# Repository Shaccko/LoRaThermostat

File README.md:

# LoRaThermostat
A 24V HVAC designed Thermostat built using the STM32 F103C8T6

By Ghanim

This is my first big capstone project, and it was done over the course of my final 
year in computer science. Unfortunately no git commits since I wasn't wise enough
back then to have initialized this project with git, so it's as raw as it gets.

This was made out of necessity, not as a desire to learn (which changed over its duration)
because my thermostat at home was 8 steps away from my room, and I hated having to get up
and change it manually due to people at my home constantly changing it. I thought it would
be nice to have a thermostat with a remote, and coincidentally at the time I was just getting
into my very first introduction to embedded design thats not arduino, with the STM32. I was also
incredibly curious as to how people exactly make the transition from MCU prototype to actual
PCB design.

# Device/Components used
# STM32 F103C8T6
For the MCU, initially I went way overkill and started with the F746ZGT6U family,
which provided 1MB flash and 512kb sram, incredibly overkill with what 
the project intended to be. As I moved to PCB design, this was switched to the F103
family for reduced chip cost, and redo'ing pretty much everything.

# LoRa
This was also my first introduction to LoRa, it was perfect for what my design was
intended for, a transmitter (remote) transmitting at most up to 10 bytes intended
for long range uses. I used a random LoRa library online I found at the time, since
bits were too scary to work with, although going back I definitely wish I'd have
read the LoRa datasheet atleast since it would have shown me different optimization modes
LoRa offers, like sleep mode, receiving a single packet, optimizing current draw etc.

# Si7021/JHD204a
To actually read and display temperature, I used the Si7021 Honeywell module, and the JHD204a
20x4 liquid crystal, controlling both with their own library I found online. 

# Main application design
I wish I did initialize this project with git when I started, because it really would be nice to look
at how disorganized my code first seemed compared to how it is now (relatively, atleast).
Receiver and Transmitter are separated under their own projects. 
Transmitter and receiver both run a state machine and constantly check for LoRa commands from either side.
Transmitter sends a metadata guarded buffer via LoRa to be decoded by receiver. The thermostat goes to sleep
if no commands are received within a duration, the MCU goes to sleep 
by employing STM32's STOP mode, turns off LCD backlight, and wakes up via external interrupts/every 50 seconds. 
STOP mode was configured so as to save as much power as possible during moments of no operations, even though LoRa being in receive continuous mode 
draws moderately more power, the MCU balances its own current draw by going to sleep. 

Temperature is moderated using a 'deadzone' mechanic so as to prevent rapid cool/heat furnace mode which could cause issues. If temperature
is set to cool or heat, but below/above its setpoint, it waits till it crosses setpoint plus or minus its deadzone, then
only it turns on either heat or ac. For the small duration it wakes up, it sends current temperature data back to transmitter,
making sure both modules are in sync. This design philosophy was inspired by observing my current Honeywell thermostat.

# PCB/Schematic Design
This portion took pretty much 60% of the total project time. It was my first introduction to 
pcb design and I wanted to be absolutely 100% sure that I wouldn't mess anything up (due to 
high pcb design cost, atleast from JLCPCB) , and took my time learning the basics of 
electronic design.

# STM32 Schematic
Following Phils Lab intro to KiCad with STM32 guide, I was able to make initial
schematic designs that fit the bare essentials of what a PCB with an embedded MCU would need: crystal,
capacitors, boot modes, and power supply. 

# Transmitter (Remote)
# Transmitter MCU

A 100n capacitor is installed per VDD pin, as per STM32's MCU design guide. An 8MHz crystal is used, matching what my MCU
prototype was using, and a boot mode switch, which pulls BOOT0 either high or low depending on programming/flash mode.
To program it, we use ST-LINK, 4 male pins are exposed to STM32's SWCLK and SWDIO for programming.
Receiver's MCU looks exact same, only difference is different pinout locations. 

# Power Supply

Simple USB-C 5.0V to 3.3V power supply. Uses a cheap LDO regulator, the AMS1117-3.3v to convert 5.0v to 3.3v.

# Components

Other than buttons, both LoRa and the JHD204a LCD were substituted with female header pins for budget reasons; I already
had their respective breakout modules at home, so it was a matter of just simply attaching them to their respective headers.

# Receiver (Thermostat)
# Receiver MCU
Same as transmitter.

# Power supply

Our thermostat wants to be attached to a wall practically, so I went with a 2x Double A battery as input. This in turn is supplied to a 
boost convertor, texas instruments TPS6104 that ramps up voltage to 5.0v, and back to a stable 3.3v using the same LDO regulator to supply 
a stable 3.3v to our circuit. Looking back at it, a separate power supply strategy using batteries should have been used instead,
converting to 5.0v then back to 3.3v is definitely not ideal. Regardless, when I was designing this, I made sure to ensure that I would
achieve atleast 90% efficiency. TPS6104 is designed to be quiescient, meaning minimal battery current usage during stages of low circuit
overall draw. 

# Triac -> SSR for HVAC Routing

This circuit is responsible for safely sending MCU high/low signals to our HVAC24 system. If heat/cool signals high, voltage reaches
our opto-triac, which in turn signals our triac to open gate and let flow 24V from R line from our furnace. Every half-cycle it checks
if signal is high, and as soon as MCU signals low, on its next half-cycle, the triac will shut its gate down and not let current flow.

Previously, I had a much simpler relay design in mind, where I would use a relay for each temperature pin to signal HVAC to turn heat/cool,
but this was discarded as the current drawage was way too high, and battery would drain very quick, only lasting ~2-3hrs. Our OPTO-Triac consumes
MCU's pin signal current only, consuming at most ~10mA. An accompanying 100k resistor snub is supplied as well, just in-case for unecessary noise
pulling in and accidently opening up our triac gate. 

# Components

Same as remote, except for the addition of our Si7021 Temp Sensor. Has two 10k resistors supplied as per its recommended datasheet design.

# PCB Design
I won't be talking much about component placement, I will highlight only core PCB design concepts I followed.
The entire circuit has a back GND copper layer, ideal for low impedance and easy to route GND for components.

# Transmitter (Remote)

Remote battery supply. Get's a 5.0v rating from a USB-C port, supplied to LCD for 5.0v, converted to 3.3v via LDO regulator.

# Receiver (Thermostat)

Decoupling caps need to be placed as close as they can be to the circuit it is connected to so as to absorb noise and prevent
high inductance from long loops.

SPI Signals were traced so that they wouldn't come too close to one another, especially SPI_SCK. High MHz signals can cause noise and
crosstalk and they must be separate from other signals.

On LoRa's GND connections, a GND copper pour was put in for imepdance control, with plenty of GND via stitching.

Battery supply layout. Nothing special, simply followed TPS6104's example layout.

This terminal takes the 24VAC's cool/heat/R wires. 

# Final Result
Surprisingly, my first PCB order I made was working 100%, both receiver and transmitter. I tested it by actually replacing my in-house
thermostat with this one for a good hour. Temperature was raised, turned off, lowered, heat, cooling, everything was working sound.
I wasn't confident enough however to leave it on for longer time or an entire day, I still trust a commerically designed thermostat
over my amateur one.

# Thoughts
This was a great project to get introduced to pcb design, basic electronics, and high level MCU design. 
I jumped straight to making an LED blink to creating this monster of a project, the learning curve was enormous,
but much was learned, and I am grateful I stuck through it.

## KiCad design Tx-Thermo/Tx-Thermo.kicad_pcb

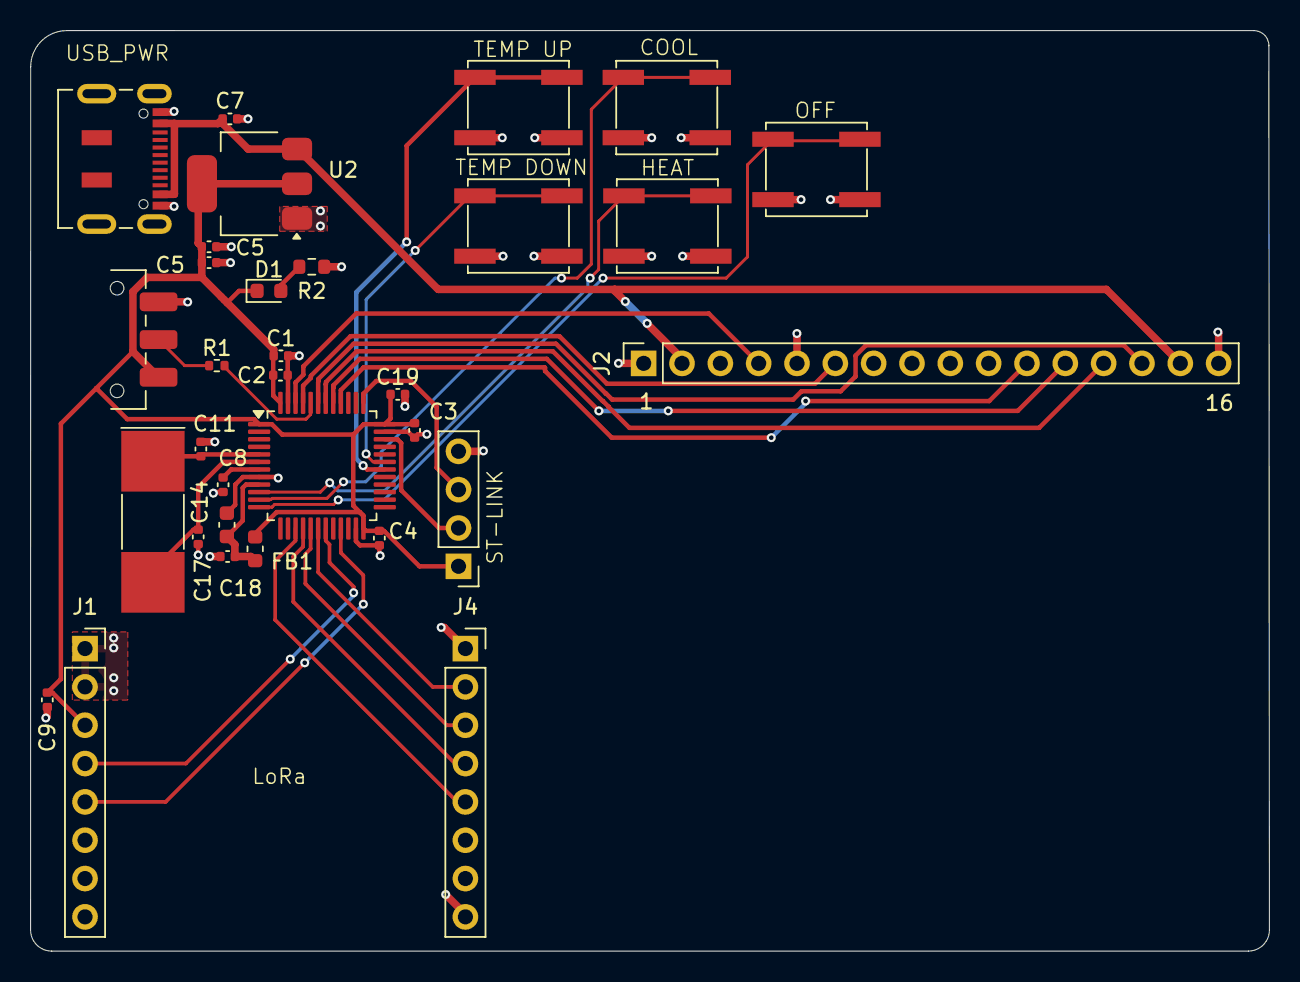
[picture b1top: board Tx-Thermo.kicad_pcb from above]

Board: 2 copper layers, 82.1 x 61.0 mm, 32 parts (0 on the bottom side), 29 nets.

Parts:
C1, C5, C7: 10u; C_0402_1005Metric
C2, C3, C4, C8: 100n; C_0402_1005Metric
C5#2, C9, C11, C14: 10p; C_0402_1005Metric
C17: 10n; C_0603_1608Metric
C18, C19: 1u; C_0402_1005Metric
D1: LED; LED_0603_1608Metric
FB1: 120R; L_0603_1608Metric
J1: LoRa_Left; PinSocket_1x08_P2.54mm_Vertical
J2: Conn_01x16; PinSocket_1x16_P2.54mm_Vertical
J3: Conn_01x04_Pin; PinHeader_1x04_P2.54mm_Vertical
J4: LoRa_Right; PinSocket_1x08_P2.54mm_Vertical
P1: USB_C_Plug; USB_C_Receptacle_JAE_DX07S016JA1R1500
R1: 10k; R_0402_1005Metric
R2: 1k5; R_0603_1608Metric
SW1: SW_SPDT; SW_SPDT_CK_JS102011SAQN
SW2: Off_State; SW_SPST_EVQP0
SW3: AC_On; SW_SPST_EVQP0
SW4: Heat_On; SW_SPST_EVQP0
SW5: Temp_Down; SW_SPST_EVQP0
SW6: Temp_Up; SW_SPST_EVQP0
U2: AMS1117-3.3; SOT-223-3_TabPin2
U6: STM32F103C8Tx; LQFP-48_7x7mm_P0.5mm
Y2: 8MHz; Crystal_SMD_MicroCrystal_CC1V-T1A-2Pin_8.0x3.7mm_HandSolder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

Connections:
+3.3V: C1.1, C2.1, C3.1, C4.1, C5.1, C5#2.2, C9.2, C19.1, D1.1 (K), FB1.2, J1.3, J3.1, SW1.3 (C), U2.2 (VO), U6.1 (VBAT), U6.24 (VDD), U6.36 (VDD), U6.48 (VDD)
+3.3VA: C17.1, C18.1, FB1.1, U6.9 (VDDA)
+5V: C7.1, J2.2, J2.15, P1.A4 (VBUS), P1.A9 (VBUS), P1.B4 (VBUS), P1.B9 (VBUS), U2.3 (VI)
/AC_Pin: SW3.1, U6.11 (PA1)
/DIO0: J1.5, U6.21 (PB10)
/HSE_IN: C11.1, U6.5 (PD0), Y2.1
/HSE_OUT: C14.1, U6.6 (PD1), Y2.2
/Heat_Pin: SW4.1, U6.10 (PA0)
/LCD_D4: J2.14, U6.43 (PB7)
/LCD_D5: J2.13, U6.42 (PB6)
/LCD_D6: J2.12, U6.41 (PB5)
/LCD_D7: J2.11, U6.40 (PB4)
/LCD_E: J2.6, U6.45 (PB8)
/LCD_RS: J2.4, U6.46 (PB9)
/NRST: C8.2, U6.7 (NRST)
/NSS: J4.2, U6.18 (PB0)
/Off_Pin: SW2.1, U6.12 (PA2)
/RST: J1.4, U6.19 (PB1)
/SPI1_MISO: J4.4, U6.16 (PA6)
/SPI1_MOSI: J4.3, U6.17 (PA7)
/SPI1_SCK: J4.5, U6.15 (PA5)
/SWCLK: J3.3, U6.37 (PA14)
/SWDIO: J3.2, U6.34 (PA13)
/SW_BOOT0: R1.1, SW1.2 (B)
/Temp_D_Pin: SW5.1, U6.31 (PA10)
/Temp_U_Pin: SW6.1, U6.30 (PA9)
GND: C1.2, C2.2, C3.2, C4.2, C5.2, C5#2.1, C7.2, C8.1, C9.1, C11.2, C14.2, C17.2, C18.2, C19.2, J1.1, J1.2, J2.1, J2.5, J2.16, J3.4, J4.1, J4.8, P1.A1 (GND), P1.A12 (GND), P1.B1 (GND), P1.B12 (GND), R2.1, SW1.1 (A), SW2.2, SW3.2, SW4.2, SW5.2, SW6.2, U2.1 (GND), U6.8 (VSSA), U6.23 (VSS), U6.35 (VSS), U6.47 (VSS)
unnamed: D1.2 (A), R2.2
unnamed: R1.2, U6.44 (BOOT0)

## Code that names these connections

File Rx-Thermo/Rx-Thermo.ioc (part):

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Mcu.Name=STM32F103C(8-B)Tx
Mcu.Package=LQFP48
Mcu.UserName=STM32F103C8Tx
PA1.Signal=GPIO_Output
PA10.GPIOParameters=PinState,GPIO_Label
PA10.GPIO_Label=LCD_BACKLIGHT
PA10.PinState=GPIO_PIN_RESET
PA10.Signal=GPIO_Output
PA11.GPIOParameters=GPIO_Label
PA11.GPIO_Label=TEMP_DOWN
PA11.Signal=GPIO_Output
PA13.Mode=Serial_Wire
PA13.Signal=SYS_JTMS-SWDIO
PA14.Mode=Serial_Wire
PA14.Signal=SYS_JTCK-SWCLK
PA2.Signal=GPIO_Output
PA5.Mode=Full_Duplex_Master
PA5.Signal=SPI1_SCK
PA6.Mode=Full_Duplex_Master
PA6.Signal=SPI1_MISO
PA7.Mode=Full_Duplex_Master
PA7.Signal=SPI1_MOSI
PA8.GPIOParameters=GPIO_Label
PA8.GPIO_Label=AC
PA8.Signal=GPIO_Output
PA9.GPIOParameters=GPIO_Label
PA9.GPIO_Label=TEMP_UP
PA9.Signal=GPIO_Output
PB0.GPIOParameters=PinState,GPIO_Label
PB0.GPIO_Label=NSS
PB0.PinState=GPIO_PIN_SET
PB0.Signal=GPIO_Output
PB1.GPIOParameters=PinState,GPIO_Label
PB1.GPIO_Label=RST
PB1.PinState=GPIO_PIN_SET
PB1.Signal=GPIO_Output
PB10.GPIOParameters=GPIO_PuPd,GPIO_Label
PB10.GPIO_Label=DIO0
PB10.GPIO_PuPd=GPIO_PULLDOWN
PB10.Signal=GPXTI10
PB12.GPIOParameters=GPIO_Label
PB12.GPIO_Label=OFF
PB12.Signal=GPIO_Output
PB13.GPIOParameters=GPIO_Label
PB13.GPIO_Label=HEAT
PB13.Signal=GPIO_Output
PB8.Mode=I2C
PB8.Signal=I2C1_SCL
PB9.Mode=I2C
PB9.Signal=I2C1_SDA
PC13-TAMPER-RTC.Mode=RTC OUT
PC13-TAMPER-RTC.Signal=RTC_OUT
PD0-OSC_IN.Mode=HSE-External-Oscillator
PD0-OSC_IN.Signal=RCC_OSC_IN
PD1-OSC_OUT.Mode=HSE-External-Oscillator
PD1-OSC_OUT.Signal=RCC_OSC_OUT
RCC.SYSCLKFreq_VALUE=72000000
RCC.SYSCLKSource=RCC_SYSCLKSOURCE_PLLCLK
board=custom

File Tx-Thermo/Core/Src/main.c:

/* USER CODE BEGIN Header */
/**
  ******************************************************************************
  * @file           : main.c
  * @brief          : Main program body
  ******************************************************************************
  * @attention
  *
  * Copyright (c) 2025 STMicroelectronics.
  * All rights reserved.
  *
  * This software is licensed under terms that can be found in the LICENSE file
  * in the root directory of this software component.
  * If no LICENSE file comes with this software, it is provided AS-IS.
  *
  ******************************************************************************
  */
/* USER CODE END Header */
/* Includes ------------------------------------------------------------------*/
#include "main.h"
#include "spi.h"
#include "gpio.h"

/* Private includes ----------------------------------------------------------*/
/* USER CODE BEGIN Includes */
/*--------------------TRANSMITTER--------------------*/
#include <string.h>
#include <stdio.h>
#include "stm32f1xx.h"
#include "LoRa.h"
#include <stdlib.h>
#include <LiquidCrystal.h>
#include "Tx-Commands.h"
/* USER CODE END Includes */

/* Private typedef -----------------------------------------------------------*/
/* USER CODE BEGIN PTD */

/* USER CODE END PTD */

/* Private define ------------------------------------------------------------*/
/* USER CODE BEGIN PD */
#define UNAVAILABLE -1
#define FREE 0
#define BUSY 1

#define HEAT 0
#define AC 1
#define OFF -1

#define TEMP_PORT GPIOA

#define MAX_BUTTONS 5
/* USER CODE END PD */

/* Private macro -------------------------------------------------------------*/
/* USER CODE BEGIN PM */

/* USER CODE END PM */

/* Private variables ---------------------------------------------------------*/

/* USER CODE BEGIN PV */
LoRa myLoRa;
uint16_t LoRa_stat = 0;
uint8_t RxBuffer[16];
size_t air_mode = OFF;
uint8_t temperature = 0;
uint8_t temp_setpt = 0;
volatile uint8_t rx_ready = 0;
/* USER CODE END PV */

/* Private function prototypes -----------------------------------------------*/
void SystemClock_Config(void);
static void MX_NVIC_Init(void);
/* USER CODE BEGIN PFP */
/* USER CODE END PFP */

/* Private user code ---------------------------------------------------------*/
/* USER CODE BEGIN 0 */
/* USER CODE END 0 */

/**
  * @brief  The application entry point.
  * @retval int
  */
int main(void)
{

  /* USER CODE BEGIN 1 */

  /* USER CODE END 1 */

  /* MCU Configuration--------------------------------------------------------*/

  /* Reset of all peripherals, Initializes the Flash interface and the Systick. */
  HAL_Init();

  /* USER CODE BEGIN Init */

  /* USER CODE END Init */

  /* Configure the system clock */
  SystemClock_Config();

  /* USER CODE BEGIN SysInit */

  /* USER CODE END SysInit */

  /* Initialize all configured peripherals */
  MX_GPIO_Init();
  MX_SPI1_Init();

  /* Initialize interrupts */
  MX_NVIC_Init();
  /* USER CODE BEGIN 2 */



  myLoRa = newLoRa();
  myLoRa.hSPIx = &hspi1;
  myLoRa.CS_port = GPIOB;
  myLoRa.CS_pin = GPIO_PIN_0;
  myLoRa.reset_port = GPIOB;
  myLoRa.reset_pin = GPIO_PIN_1;
  myLoRa.DIO0_port = GPIOB;
  myLoRa.DIO0_pin = GPIO_PIN_10;

  if (LoRa_init(&myLoRa) != LORA_OK) {
	  print("LoRa Failed!");
  }
  LoRa_stat = 1;

  LiquidCrystal(GPIOB, LCD_RS_Pin, 255, LCD_E_Pin,
		  LCD_D7_Pin, LCD_D6_Pin, LCD_D5_Pin, LCD_D4_Pin);
  Buttons button[] = {
		  {FREE, Get_TempUpButtonState, TransmitTEMPUPCommand},
		  {FREE, Get_TempDownButtonState, TransmitTEMPDOWNCommand},
		  {FREE, Get_HeatButtonState, TransmitHEATCommand},
		  {FREE, Get_ACButtonState, TransmitACCommand},
		  {FREE, Get_OffButtonState, TransmitOFFCommand}
  };
  air_mode = OFF;
  char* command;
  LCD_StrInit();
  LoRa_startReceiving(&myLoRa);

  /* USER CODE END 2 */

  /* Infinite loop */
  /* USER CODE BEGIN WHILE */
  while (1)
  {
    /* USER CODE END WHILE */

    /* USER CODE BEGIN 3 */
	  size_t i;
	  if (rx_ready) {
		  command = (char*) RxBuffer;
		  rx_ready = 0;
		  if (atoi(command) != 0) {
			  uint16_t tmp = atoi(command);
			  /* We receive 16 bits, upper 8 bits hold temp, lower 8 bits hold setpoint*/
			  temp_setpt = tmp & 0xFF;
			  temperature = (tmp >> 8) & 0xFF;
			  LCD_UpdateSetpt();
			  LCD_UpdateTemp();
		  }
	  }

	  for (i = 0; i < MAX_BUTTONS; i++) {
		  if (button[i].GetPinState() == FREE && button[i].state == FREE) {
			  button[i].state = BUSY;
			  if (button[i].TransmitMessage()) {
				  /* some success message */
			  }
			  else {
				  /* some failure message */
			  }
		  }

		  if (button[i].GetPinState() == BUSY && button[i].state == BUSY) {
			  button[i].state = FREE;
		  }
		  memset(RxBuffer, 0, sizeof(RxBuffer));
		  HAL_Delay(10); /* Debouncing */

	  }
  }
  /* USER CODE END 3 */
}

/**
  * @brief System Clock Configuration
  * @retval None
  */
void SystemClock_Config(void)
{
  RCC_OscInitTypeDef RCC_OscInitStruct = {0};
  RCC_ClkInitTypeDef RCC_ClkInitStruct = {0};

  /** Initializes the RCC Oscillators according to the specified parameters
  * in the RCC_OscInitTypeDef structure.
  */
  RCC_OscInitStruct.OscillatorType = RCC_OSCILLATORTYPE_HSE;
  RCC_OscInitStruct.HSEState = RCC_HSE_ON;
  RCC_OscInitStruct.HSEPredivValue = RCC_HSE_PREDIV_DIV1;
  RCC_OscInitStruct.HSIState = RCC_HSI_ON;
  RCC_OscInitStruct.PLL.PLLState = RCC_PLL_ON;
  RCC_OscInitStruct.PLL.PLLSource = RCC_PLLSOURCE_HSE;
  RCC_OscInitStruct.PLL.PLLMUL = RCC_PLL_MUL9;
  if (HAL_RCC_OscConfig(&RCC_OscInitStruct) != HAL_OK)
  {
    Error_Handler();
  }

  /** Initializes the CPU, AHB and APB buses clocks
  */
  RCC_ClkInitStruct.ClockType = RCC_CLOCKTYPE_HCLK|RCC_CLOCKTYPE_SYSCLK
                              |RCC_CLOCKTYPE_PCLK1|RCC_CLOCKTYPE_PCLK2;
  RCC_ClkInitStruct.SYSCLKSource = RCC_SYSCLKSOURCE_PLLCLK;
  RCC_ClkInitStruct.AHBCLKDivider = RCC_SYSCLK_DIV1;
  RCC_ClkInitStruct.APB1CLKDivider = RCC_HCLK_DIV2;
  RCC_ClkInitStruct.APB2CLKDivider = RCC_HCLK_DIV1;

  if (HAL_RCC_ClockConfig(&RCC_ClkInitStruct, FLASH_LATENCY_2) != HAL_OK)
  {
    Error_Handler();
  }
}

/**
  * @brief NVIC Configuration.
  * @retval None
  */
static void MX_NVIC_Init(void)
{
  /* SPI1_IRQn interrupt configuration */
  HAL_NVIC_SetPriority(SPI1_IRQn, 0, 0);
  HAL_NVIC_EnableIRQ(SPI1_IRQn);
  /* EXTI15_10_IRQn interrupt configuration */
  HAL_NVIC_SetPriority(EXTI15_10_IRQn, 0, 0);
  HAL_NVIC_EnableIRQ(EXTI15_10_IRQn);
}

/* USER CODE BEGIN 4 */

void HAL_GPIO_EXTI_Callback(uint16_t GPIO_Pin)
{
	if (GPIO_Pin == DIO0_Pin) {
		LoRa_receive(&myLoRa, RxBuffer, 16);
		rx_ready = 1;
	}
}

/* USER CODE END 4 */

/**
  * @brief  This function is executed in case of error occurrence.
  * @retval None
  */
void Error_Handler(void)
{
  /* USER CODE BEGIN Error_Handler_Debug */
  /* User can add his own implementation to report the HAL error return state */
  __disable_irq();
  while (1)
  {
  }
  /* USER CODE END Error_Handler_Debug */
}

#ifdef  USE_FULL_ASSERT
/**
  * @brief  Reports the name of the source file and the source line number
  *         where the assert_param error has occurred.
  * @param  file: pointer to the source file name
  * @param  line: assert_param error line source number
  * @retval None
  */
void assert_failed(uint8_t *file, uint32_t line)
{
  /* USER CODE BEGIN 6 */
  /* User can add his own implementation to report the file name and line number,
     ex: printf("Wrong parameters value: file %s on line %d\r\n", file, line) */
  /* USER CODE END 6 */
}
#endif /* USE_FULL_ASSERT */

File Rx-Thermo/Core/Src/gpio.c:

/* USER CODE BEGIN Header */
/**
  ******************************************************************************
  * @file    gpio.c
  * @brief   This file provides code for the configuration
  *          of all used GPIO pins.
  ******************************************************************************
  * @attention
  *
  * Copyright (c) 2025 STMicroelectronics.
  * All rights reserved.
  *
  * This software is licensed under terms that can be found in the LICENSE file
  * in the root directory of this software component.
  * If no LICENSE file comes with this software, it is provided AS-IS.
  *
  ******************************************************************************
  */
/* USER CODE END Header */

/* Includes ------------------------------------------------------------------*/
#include "gpio.h"

/* USER CODE BEGIN 0 */

/* USER CODE END 0 */

/*----------------------------------------------------------------------------*/
/* Configure GPIO                                                             */
/*----------------------------------------------------------------------------*/
/* USER CODE BEGIN 1 */

/* USER CODE END 1 */

/** Configure pins as
        * Analog
        * Input
        * Output
        * EVENT_OUT
        * EXTI
*/
void MX_GPIO_Init(void)
{

  GPIO_InitTypeDef GPIO_InitStruct = {0};

  /* GPIO Ports Clock Enable */
  __HAL_RCC_GPIOC_CLK_ENABLE();
  __HAL_RCC_GPIOD_CLK_ENABLE();
  __HAL_RCC_GPIOA_CLK_ENABLE();
  __HAL_RCC_GPIOB_CLK_ENABLE();

  /*Configure GPIO pin Output Level */
  HAL_GPIO_WritePin(GPIOA, GPIO_PIN_1|GPIO_PIN_2|AC_Pin|TEMP_UP_Pin
                          |LCD_BACKLIGHT_Pin|TEMP_DOWN_Pin, GPIO_PIN_RESET);

  /*Configure GPIO pin Output Level */
  HAL_GPIO_WritePin(GPIOB, NSS_Pin|RST_Pin, GPIO_PIN_SET);

  /*Configure GPIO pin Output Level */
  HAL_GPIO_WritePin(GPIOB, OFF_Pin|HEAT_Pin, GPIO_PIN_RESET);

  /*Configure GPIO pins : PA1 PA2 PAPin PAPin
                           PAPin PAPin */
  GPIO_InitStruct.Pin = GPIO_PIN_1|GPIO_PIN_2|AC_Pin|TEMP_UP_Pin
                          |LCD_BACKLIGHT_Pin|TEMP_DOWN_Pin;
  GPIO_InitStruct.Mode = GPIO_MODE_OUTPUT_PP;
  GPIO_InitStruct.Pull = GPIO_NOPULL;
  GPIO_InitStruct.Speed = GPIO_SPEED_FREQ_LOW;
  HAL_GPIO_Init(GPIOA, &GPIO_InitStruct);

  /*Configure GPIO pins : PBPin PBPin PBPin PBPin */
  GPIO_InitStruct.Pin = NSS_Pin|RST_Pin|OFF_Pin|HEAT_Pin;
  GPIO_InitStruct.Mode = GPIO_MODE_OUTPUT_PP;
  GPIO_InitStruct.Pull = GPIO_NOPULL;
  GPIO_InitStruct.Speed = GPIO_SPEED_FREQ_LOW;
  HAL_GPIO_Init(GPIOB, &GPIO_InitStruct);

  /*Configure GPIO pin : PtPin */
  GPIO_InitStruct.Pin = DIO0_Pin;
  GPIO_InitStruct.Mode = GPIO_MODE_IT_RISING;
  GPIO_InitStruct.Pull = GPIO_PULLDOWN;
  HAL_GPIO_Init(DIO0_GPIO_Port, &GPIO_InitStruct);

}

/* USER CODE BEGIN 2 */

/* USER CODE END 2 */

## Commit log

2026-01-05 Added PCB pics
